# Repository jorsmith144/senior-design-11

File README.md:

# senior-dorrsign
Project 11 PEQ (working title) Github repository for real time audio processor

Github repositroy for all code and KiCad Files
- TODO KiCad library
- I2C Code
- I2S Code (Double Buffering if we are cool)
- DSP Code
- idk
- GUI Code

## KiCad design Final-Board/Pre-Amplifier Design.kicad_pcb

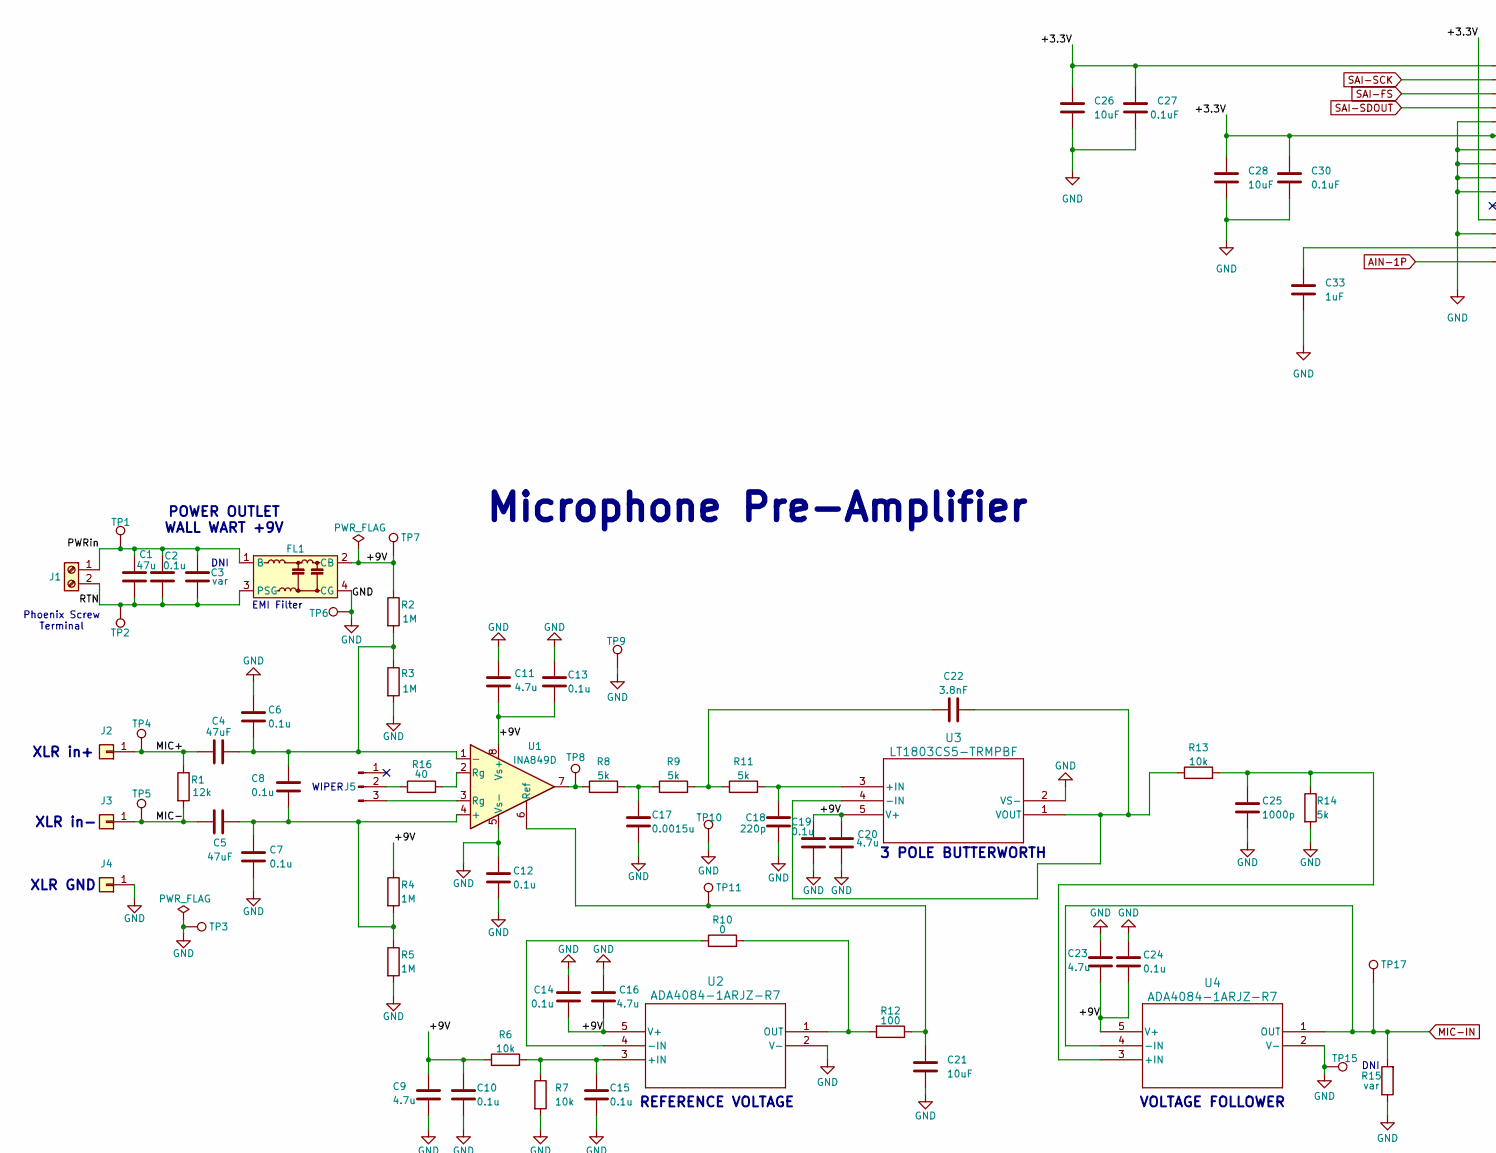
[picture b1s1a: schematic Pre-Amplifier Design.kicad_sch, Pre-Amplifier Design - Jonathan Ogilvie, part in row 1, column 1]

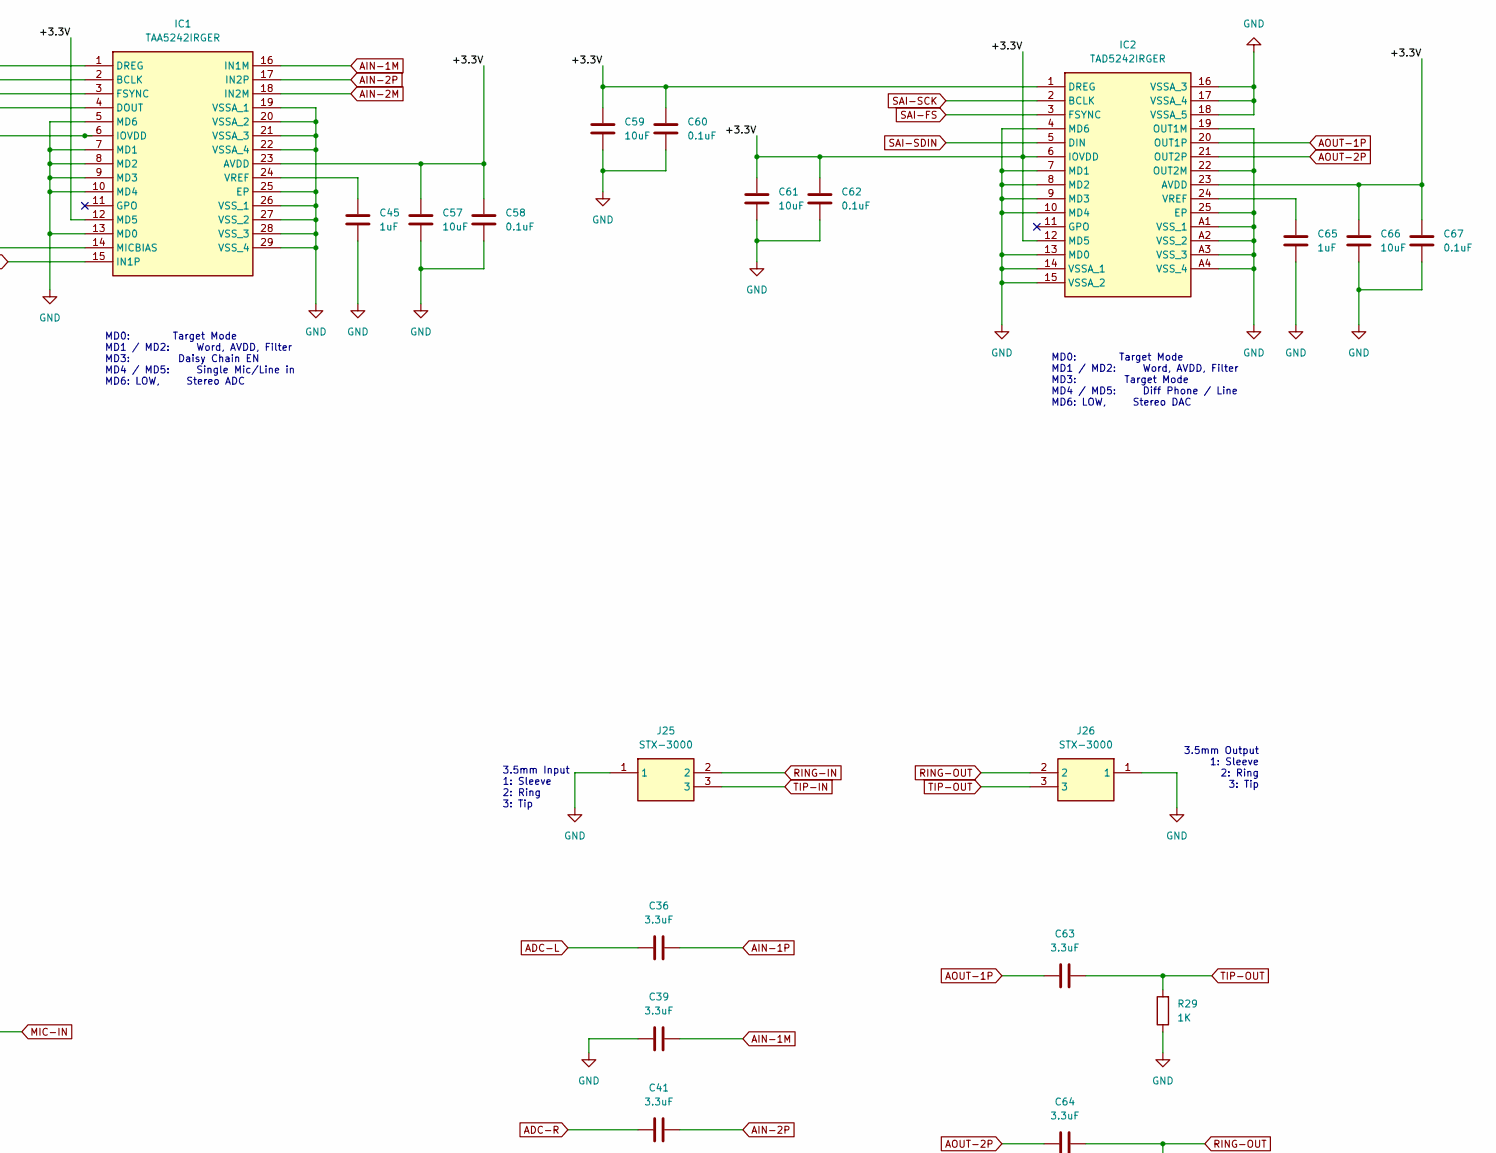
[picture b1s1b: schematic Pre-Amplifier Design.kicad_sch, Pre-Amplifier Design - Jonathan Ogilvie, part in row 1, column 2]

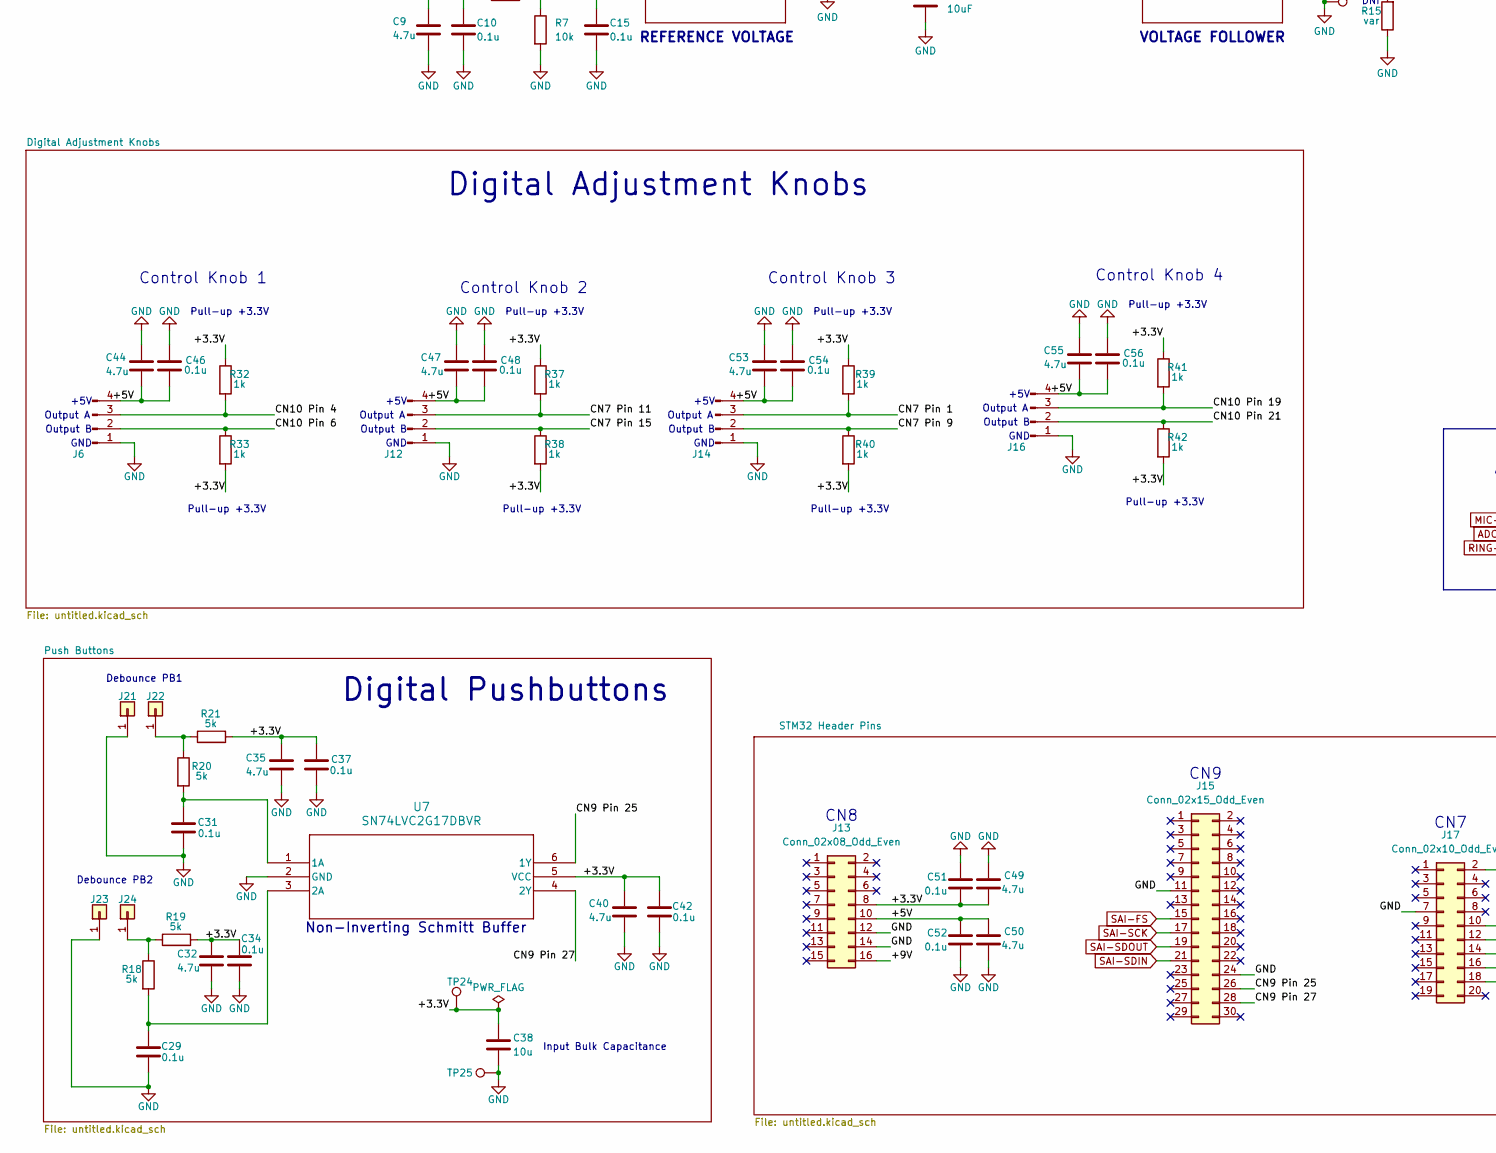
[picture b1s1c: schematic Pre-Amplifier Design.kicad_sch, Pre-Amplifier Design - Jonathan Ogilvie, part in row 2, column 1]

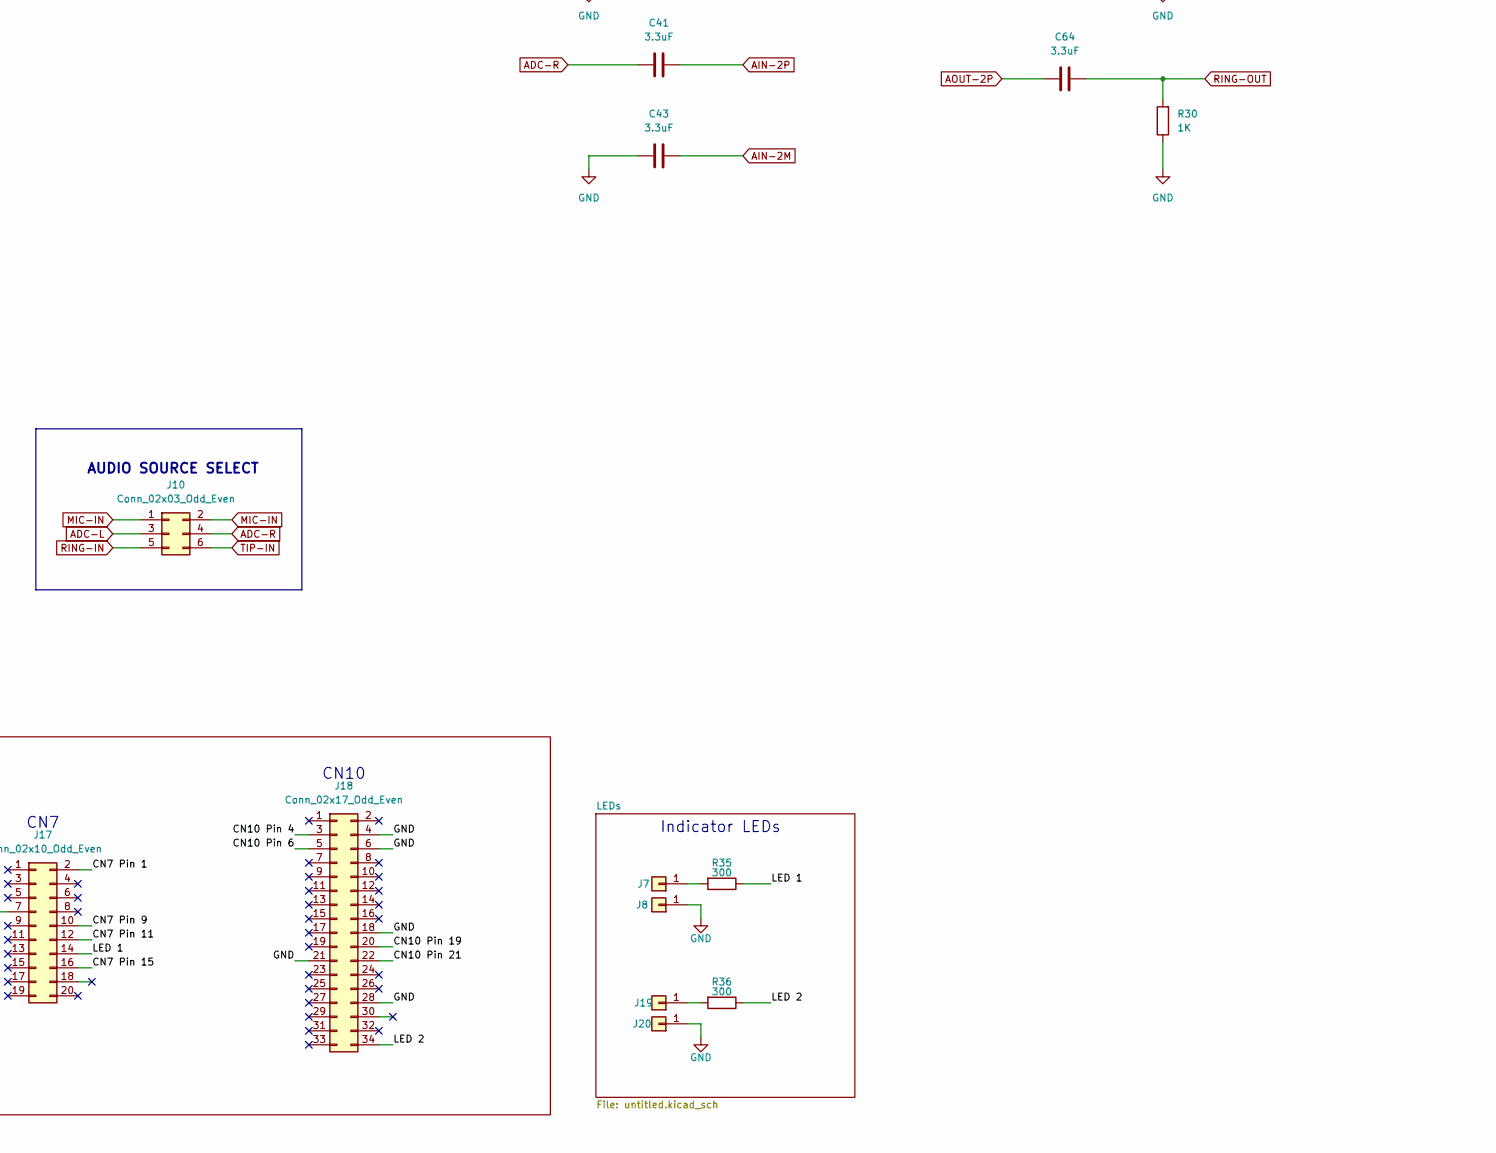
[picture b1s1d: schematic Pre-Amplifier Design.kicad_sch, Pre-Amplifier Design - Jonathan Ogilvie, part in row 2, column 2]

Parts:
C1: 47u; C_1206_3216Metric_Pad1.33x1.80mm_HandSolder
C2, C6, C7, C8, C10, C12, C13, C14, C15, C19, C24, C29, C31, C34, C37, C42, C46, C48, C51, C52, C54, C56: 0.1u; C_0603_1608Metric_Pad1.08x0.95mm_HandSolder
C3: var; C_0603_1608Metric_Pad1.08x0.95mm_HandSolder
C4, C5: 47uF; C_1206_3216Metric_Pad1.33x1.80mm_HandSolder
C9, C11, C16, C20, C23, C32, C35, C40, C44, C47, C49, C50, C53, C55: 4.7u; C_0603_1608Metric_Pad1.08x0.95mm_HandSolder
C17: 0.0015u; C_0603_1608Metric_Pad1.08x0.95mm_HandSolder
C18: 220p; C_0603_1608Metric_Pad1.08x0.95mm_HandSolder
C21: 10uF; C_1206_3216Metric_Pad1.33x1.80mm_HandSolder
C22: 3.8nF; C_0603_1608Metric_Pad1.08x0.95mm_HandSolder
C25: 1000p; C_0603_1608Metric_Pad1.08x0.95mm_HandSolder
C26, C28, C57, C59, C61, C66: 10uF; C_0603_1608Metric_Pad1.08x0.95mm_HandSolder
C27, C30, C58, C60, C62, C67: 0.1uF; C_0603_1608Metric_Pad1.08x0.95mm_HandSolder
C33, C45, C65: 1uF; C_0603_1608Metric_Pad1.08x0.95mm_HandSolder
C36, C39, C41, C43, C63, C64: 3.3uF; C_0603_1608Metric_Pad1.08x0.95mm_HandSolder
C38: 10u; C_1206_3216Metric_Pad1.33x1.80mm_HandSolder
FL1: BNX027; Filter_Murata_BNX025
IC1: TAA5242IRGER; Manufacturer_Part_Number TAA5242IRGER
IC2: TAD5242IRGER; Manufacturer_Part_Number TAD5242IRGER; Mouser Part Number 595-TAD5242IRGER
J1: Screw_Terminal_01x02; TerminalBlock_Phoenix_MKDS-1,5-2-5.08_1x02_P5.08mm_Horizont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
J2, J3, J4, J7, J8, J19, J20, J21, J22, J23, J24: Conn_01x01; TestPoint_THTPad_2.0x2.0mm_Drill1.0mm
J5: Conn_01x03_Pin; JST_XH_B3B-XH-A_1x03_P2.50mm_Vertical
J6, J12, J14, J16: Conn_01x04_Pin; Molex_SL_171971-0004_1x04_P2.54mm_Vertical
J10: Conn_02x03_Odd_Even; PinHeader_2x03_P2.00mm_Vertical
J13: Conn_02x08_Odd_Even; PinHeader_2x08_P2.54mm_Vertical
J15: Conn_02x15_Odd_Even; PinHeader_2x15_P2.54mm_Vertical
J17: Conn_02x10_Odd_Even; PinHeader_2x10_P2.54mm_Vertical
J18: Conn_02x17_Odd_Even; PinHeader_2x17_P2.54mm_Vertical
J25, J26: STX-3000; STX3000; Manufacturer_Part_Number STX-3000; Mouser Part Number 806-STX-3000
R1: 12k; R_0603_1608Metric_Pad0.98x0.95mm_HandSolder
R2, R3, R4, R5: 1M; R_0603_1608Metric_Pad0.98x0.95mm_HandSolder
R6, R7, R13: 10k; R_0603_1608Metric_Pad0.98x0.95mm_HandSolder
R8, R9, R11, R14, R18, R19, R20, R21: 5k; R_0603_1608Metric_Pad0.98x0.95mm_HandSolder
R10: 0; R_0603_1608Metric_Pad0.98x0.95mm_HandSolder
R12: 100; R_0603_1608Metric_Pad0.98x0.95mm_HandSolder
R15: var; R_0603_1608Metric_Pad0.98x0.95mm_HandSolder
R16: 40; R_0603_1608Metric_Pad0.98x0.95mm_HandSolder
R29, R30: 1K; R_0603_1608Metric_Pad0.98x0.95mm_HandSolder
R32, R33, R37, R38, R39, R40, R41, R42: 1k; R_0603_1608Metric_Pad0.98x0.95mm_HandSolder
R35, R36: 300; R_0603_1608Metric_Pad0.98x0.95mm_HandSolder
TP1, TP2: TestPoint; TestPoint_Plated_Hole_D3.0mm
TP3, TP4, TP5, TP6, TP7, TP8, TP9, TP10, TP11, TP15, TP17: TestPoint; TestPoint_Keystone_5005-5009_Compact
TP24, TP25: TestPoint; TestPoint_THTPad_D1.0mm_Drill0.5mm
U1: INA849D; SOIC-8_3.9x4.9mm_P1.27mm
U2, U4: ADA4084-1ARJZ-R7; SOT-23-5_HandSoldering
U3: LT1803CS5-TRMPBF; SOT-23-5_HandSoldering
U7: SN74LVC2G17DBVR; SOT-23-6_Handsoldering

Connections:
/+3.3V: C26.1, C27.1, C28.1, C30.1, C32.1, C34.2, C35.1, C37.1, C38.1, C40.1, C42.2, C49.2, C51.2, C57.1, C58.1, C59.1, C60.1, C61.1, C62.1, C66.1, C67.1, IC1.1 (DREG), IC1.6 (IOVDD), IC1.12 (MD5), IC1.23 (AVDD), IC2.1 (DREG), IC2.6 (IOVDD), IC2.12 (MD5), IC2.23 (AVDD), J13.8, R19.2, R21.2, R32.1, R33.2, R37.1, R38.2, R39.1, R40.2, R41.1, R42.2, TP24.1, U7.5 (VCC)
/+5V: C44.2, C46.2, C47.2, C48.2, C50.1, C52.1, C53.2, C54.2, C55.2, C56.2, J6.4, J12.4, J13.10, J14.4, J16.4
/+9V: C9.1, C10.1, C11.2, C13.2, C14.1, C16.1, C19.2, C20.1, C23.2, C24.2, FL1.2 (CB), J13.16, R2.1, R4.1, R6.1, TP7.1, U1.8 (Vs+), U2.5 (V+), U3.5 (V+), U4.5 (V+)
/CN7 Pin 1: J14.3, J17.2, R39.2
/CN7 Pin 9: J14.2, J17.10, R40.1
/CN7 Pin 11: J12.3, J17.12, R37.2
/CN7 Pin 15: J12.2, J17.16, R38.1
/CN9 Pin 25: J15.26, U7.6 (1Y)
/CN9 Pin 27: J15.28, U7.4 (2Y)
/CN10 Pin 4: J6.3, J18.3, R32.2
/CN10 Pin 6: J6.2, J18.5, R33.1
/CN10 Pin 19: J16.3, J18.20, R41.2
/CN10 Pin 21: J16.2, J18.22, R42.1
/LED 1: J17.14, R35.1
/LED 2: J18.34, R36.1
/MIC+: C4.1, J2.1, R1.1, TP4.1
/MIC-: C5.1, J3.1, R1.2, TP5.1
/PWRin: C1.1, C2.1, C3.1, FL1.1 (B), J1.1, TP1.1
/RTN: C1.2, C2.2, C3.2, FL1.3 (PSG), J1.2, TP2.1
ADC-L: C36.1, J10.3
ADC-R: C41.1, J10.4
AIN-1M: C39.2, IC1.16 (IN1M)
AIN-1P: C36.2, IC1.15 (IN1P)
AIN-2M: C43.2, IC1.18 (IN2M)
AIN-2P: C41.2, IC1.17 (IN2P)
AOUT-1P: C63.1, IC2.20 (OUT1P)
AOUT-2P: C64.1, IC2.21 (OUT2P)
GND: C6.1, C7.2, C9.2, C10.2, C11.1, C12.1, C12.2, C13.1, C14.2, C15.2, C16.2, C17.2, C18.2, C19.1, C20.2, C21.2, C23.1, C24.1, C25.2, C26.2, C27.2, C28.2, C29.1, C30.2, C31.1, C32.2, C33.2, C34.1, C35.2, C37.2, C38.2, C39.1, C40.2, C42.1, C43.1, C44.1, C45.2, C46.1, C47.1, C48.1, C49.1, C50.2, C51.1, C52.2, C53.1, C54.1, C55.1, C56.1, C57.2, C58.2, C59.2, C60.2, C61.2, C62.2, C65.2, C66.2, C67.2, FL1.4 (CG), IC1.5 (MD6), IC1.7 (MD1), IC1.8 (MD2), IC1.9 (MD3), IC1.10 (MD4), IC1.13 (MD0), IC1.19 (VSSA_1), IC1.20 (VSSA_2), IC1.21 (VSSA_3), IC1.22 (VSSA_4), IC1.25 (EP), IC1.26 (VSS_1), IC1.27 (VSS_2), IC1.28 (VSS_3), IC1.29 (VSS_4), IC2.4 (MD6), IC2.7 (MD1), IC2.8 (MD2), IC2.9 (MD3), IC2.10 (MD4), IC2.13 (MD0), IC2.14 (VSSA_1), IC2.15 (VSSA_2), IC2.16 (VSSA_3), IC2.17 (VSSA_4), IC2.18 (VSSA_5), IC2.19 (OUT1M), IC2.22 (OUT2M), IC2.25 (EP), IC2.A1 (VSS_1), IC2.A2 (VSS_2), IC2.A3 (VSS_3), IC2.A4 (VSS_4), J4.1, J6.1, J8.1, J12.1, J13.12, J13.14, J14.1, J15.11, J15.24, J16.1, J17.7, J18.4, J18.6, J18.18, J18.21, J18.28, J20.1, J21.1, J23.1, J25.1, J26.1, R3.2, R5.2, R7.2, R14.2, R15.1, R29.1, R30.1, TP3.1, TP6.1, TP9.1, TP10.1, TP15.1, TP25.1, U1.5 (Vs-), U2.2 (V-), U3.2 (VS-), U4.2 (V-), U7.2 (GND)
MIC-IN: J10.1, J10.2, R15.2, TP17.1, U4.1 (OUT), U4.4 (-IN)
unnamed: C17.1, R8.2, R9.1
unnamed: C22.1, R9.2, R11.1
unnamed: C33.1, IC1.14 (MICBIAS)
unnamed: C45.1, IC1.24 (VREF)
unnamed: C65.1, IC2.24 (VREF)
unnamed: J5.2, R16.1
unnamed: J5.3, U1.3 (Rg)
unnamed: J7.1, R35.2
unnamed: J19.1, R36.2
unnamed: J22.1, R20.1, R21.1
unnamed: J24.1, R18.1, R19.1
unnamed: R8.1, TP8.1, U1.7
unnamed: R16.2, U1.2 (Rg)
unnamed: C5.2, C7.1, C8.2, R4.2, R5.1, U1.4 (+)
unnamed: C4.2, C6.2, C8.1, R2.2, R3.1, U1.1 (-)
unnamed: C21.1, R12.1, TP11.1, U1.6 (Ref)
unnamed: C15.1, R6.2, R7.1, U2.3 (+IN)
unnamed: R10.1, U2.4 (-IN)
unnamed: R10.2, R12.2, U2.1 (OUT)
unnamed: C18.1, R11.2, U3.3 (+IN)
unnamed: C22.2, R13.1, U3.1 (VOUT), U3.4 (-IN)
unnamed: C25.1, R13.2, R14.1, U4.3 (+IN)
unnamed: C31.2, R20.2, U7.1 (1A)
unnamed: C29.2, R18.2, U7.3 (2A)
RING-IN: J10.5, J25.2
RING-OUT: C64.2, J26.2, R30.2
SAI-FS: IC1.3 (FSYNC), IC2.3 (FSYNC), J15.15
SAI-SCK: IC1.2 (BCLK), IC2.2 (BCLK), J15.17
SAI-SDIN: IC2.5 (DIN), J15.21
SAI-SDOUT: IC1.4 (DOUT), J15.19
TIP-IN: J10.6, J25.3
TIP-OUT: C63.2, J26.3, R29.2

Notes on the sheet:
Output A
Pull-up +3.3V
EMI Filter
DNI
CN8
CN9
Non-Inverting Schmitt Buffer
+5V
XLR in+
Debounce PB1
MD0: Target Mode MD1 / MD2: Word, AVDD, Filter MD3: Target Mode MD4 / MD5: Diff Phone / Line MD6: LOW, Stereo DAC
XLR in-
Output B
CN10
WIPER
GND
Digital Pushbuttons
REFERENCE VOLTAGE
Control Knob 4
POWER OUTLET WALL WART +9V
AUDIO SOURCE SELECT
3.5mm Output 1: Sleeve 2: Ring 3: Tip
Digital Adjustment Knobs
Input Bulk Capacitance
CN7
3 POLE BUTTERWORTH
MD0: Target Mode MD1 / MD2: Word, AVDD, Filter MD3: Daisy Chain EN MD4 / MD5: Single Mic/Line in MD6: LOW, Stereo ADC
Debounce PB2
Control Knob 2
3.5mm Input 1: Sleeve 2: Ring 3: Tip
XLR GND
Phoenix Screw Terminal
Microphone Pre-Amplifier
Control Knob 1
VOLTAGE FOLLOWER
Indicator LEDs
Control Knob 3

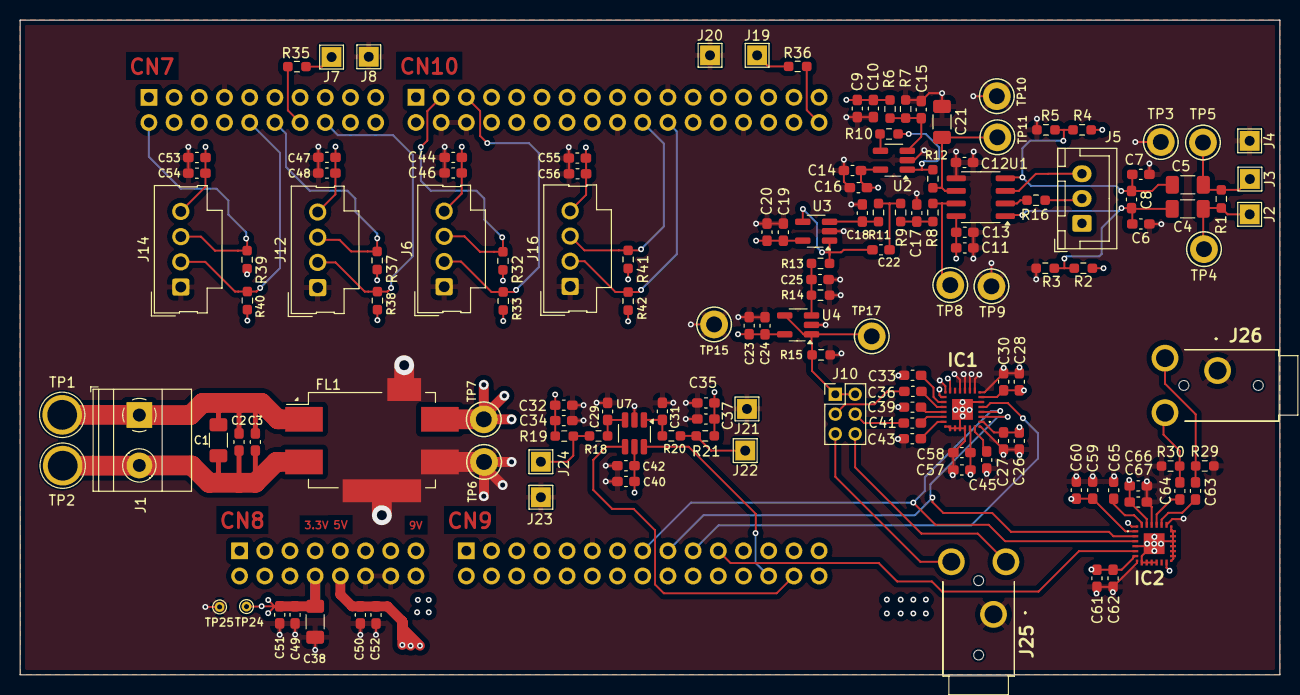
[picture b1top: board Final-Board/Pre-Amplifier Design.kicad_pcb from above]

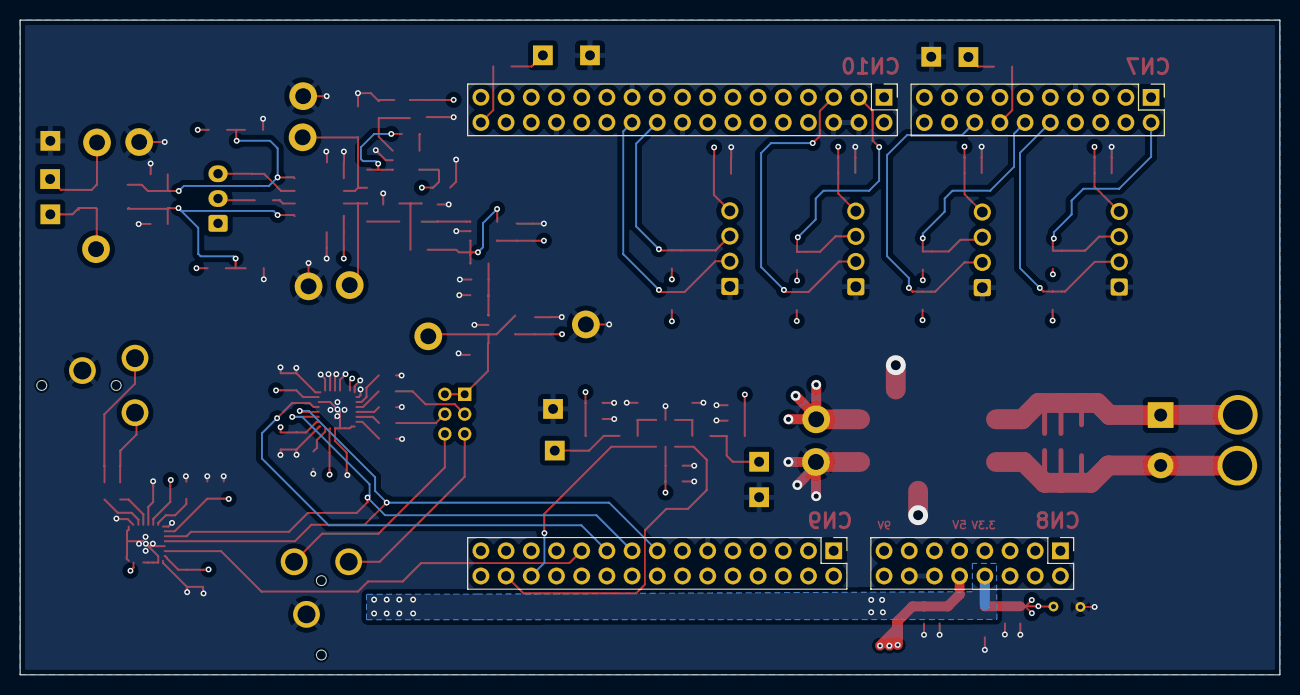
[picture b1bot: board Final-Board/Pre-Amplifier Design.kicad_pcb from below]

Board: 4 copper layers, 127.0 x 66.0 mm, 146 parts (4 on the bottom side), 61 nets.

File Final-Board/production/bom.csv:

Designator,Footprint,Quantity,Value,LCSC Part #
C1,1206,1,47u,
"C10, C12, C13, C14, C15, C19, C2, C24, C29, C31, C34, C37, C42, C46, C48, C51, C52, C54, C56, C6, C7, C8",0603,22,0.1u,
"C11, C16, C20, C23, C32, C35, C40, C44, C47, C49, C50, C53, C55, C9",0603,14,4.7u,
C17,0603,1,0.0015u,
C18,0603,1,220p,
C21,1206,1,10uF,
C22,0603,1,3.8nF,
C25,0603,1,1000p,
"C26, C28, C57, C59, C61, C66",0603,6,10uF,
"C27, C30, C58, C60, C62, C67",0603,6,0.1uF,
"C3, R15",0603,2,var,
"C33, C45, C65",0603,3,1uF,
"C36, C39, C41, C43, C63, C64",0603,6,3.3uF,
C38,1206,1,10u,
"C4, C5",1206,2,47uF,
FL1,Filter_Murata_BNX025,1,BNX027,
IC1,TAA5242IRGER,1,TAA5242IRGER,
IC2,TAD5242IRGER,1,TAD5242IRGER,
J1,"TerminalBlock_Phoenix_MKDS-1,5-2-5.08_1x02_P5.08mm_Horizontal",1,Screw_Terminal_01x02,
J10,PinHeader_2x03_P2.00mm_Vertical,1,Conn_02x03_Odd_Even,
"J12, J14, J16, J6",Molex_SL_171971-0004_1x04_P2.54mm_Vertical,4,Conn_01x04_Pin,
J13,PinHeader_2x08_P2.54mm_Vertical,1,Conn_02x08_Odd_Even,
J15,PinHeader_2x15_P2.54mm_Vertical,1,Conn_02x15_Odd_Even,
J17,PinHeader_2x10_P2.54mm_Vertical,1,Conn_02x10_Odd_Even,
J18,PinHeader_2x17_P2.54mm_Vertical,1,Conn_02x17_Odd_Even,
"J19, J2, J20, J21, J22, J23, J24, J3, J4, J7, J8",TestPoint_THTPad_2.0x2.0mm_Drill1.0mm,11,Conn_01x01,
"J25, J26",STX3000,2,STX-3000,
J5,JST_XH_B3B-XH-A_1x03_P2.50mm_Vertical,1,Conn_01x03_Pin,
R1,0603,1,12k,
R10,0603,1,0,
"R11, R14, R18, R19, R20, R21, R8, R9",0603,8,5k,
R12,0603,1,100,
"R13, R6, R7",0603,3,10k,
R16,0603,1,40,
"R2, R3, R4, R5",0603,4,1M,
"R29, R30, R32, R33, R37, R38, R39, R40, R41, R42",0603,10,1K,
"R35, R36",0603,2,300,
"TP1, TP2",TestPoint_Plated_Hole_D3.0mm,2,TestPoint,
"TP10, TP11, TP15, TP17, TP3, TP4, TP5, TP6, TP7, TP8, TP9",TestPoint_Keystone_5005-5009_Compact,11,TestPoint,
"TP24, TP25",TestPoint_THTPad_D1.0mm_Drill0.5mm,2,TestPoint,
U1,SOIC-8_3.9x4.9mm_P1.27mm,1,INA849D,
"U2, U4",SOT-23-5_HandSoldering,2,ADA4084-1ARJZ-R7,
U3,SOT-23-5_HandSoldering,1,LT1803CS5-TRMPBF,
U7,SOT-23-6_Handsoldering,1,SN74LVC2G17DBVR,
